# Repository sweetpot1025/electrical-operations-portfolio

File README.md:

# 郭浩田 · 电气工程项目作品集

**Haotian Guo | Electrical Engineering Portfolio**

河南理工大学电气工程及其自动化本科，悉尼大学电气工程硕士在读。关注电气运维、数据中心基础设施供配电、设备运行与故障分析。

项目覆盖井下供配电设计、三相电路与故障分析、电力系统动态稳定性、低压配电网全年仿真、光伏及风电实验，以及实习中的 PCB 设计和工程交付。通过手算、建模、测量和数据分析，解释从正常运行到故障、扰动及控制后的设备与系统表现。

## 项目目录

每个项目的页面包含任务、具体工作、模型或实验过程、关键结果，以及报告、数据或工程文件下载。

| 序号 | 项目 | 已完成的工作与可查看成果 |
|---|---|---|
| 01 | **[井下供配电一次系统设计](01-power-distribution-design.md)** | 本科毕设：负荷与无功分析、变压器和电缆选型、17 个短路点计算、设备校验、论文和电气主接线图 CAD |
| 02 | **[三相稳态建模、潮流与短路分析](02-short-circuit-analysis.md)** | ELEC5204：电阻/RL/非理想电源、七节点网络、三种变压器接线、三相及接地故障；两份报告和模型脚本 |
| 03 | **[单机与多机系统动态稳定性](03-dynamic-stability.md)** | ELEC5211：SMIB 功角、三机九节点潮流与无功补偿、动态初始化、故障清除、阻尼、CCT；两份报告及 23 幅成果图 |
| 04 | **[配电网、家庭储能与动态运行区间](04-distribution-network-and-storage.md)** | ELEC5208：36 用户三相四线模型、105,120 步全年分析、规则式/优化式 HEMS、SOCP DOE；三个阶段报告与工程代码 |
| 05 | **[电气测量、光伏控制与风电实验](05-energy-laboratory.md)** | ELEC5206：仪器、光伏特性、单二极管模型、PICAXE MPPT、风机测试、PMSG 联调；五份报告和测量数据 |
| 06 | **[温湿度传感器节点与 PCB 设计](06-internship-engineering.md)** | 施耐德实习：KiCad 原理图/PCB、制造与装配资料、ERC/DRC、版本复核、12 项样机验证计划 |
| 07 | **[考虑用户偏好与配网约束的 P2P 能源交易](07-capstone-research.md)** | 硕士研究进行中：研究提案、初始项目评估、交易机制及配电网约束分析 |

## 工程方法与工具

| 工作类型 | 方法与工具 |
|---|---|
| 供配电与故障 | 负荷计算、标幺制、戴维南等值、Zbus、对称分量、设备参数校验 |
| 稳态与动态建模 | MATLAB / Simulink、MATPOWER、ode45、功率平衡和相对功角分析 |
| 配电网与储能 | Julia / OpenDSS、全年时序潮流、SOC、分时电价、JuMP / HiGHS / Clarabel |
| 实验与数据 | 示波器、函数发生器、DACI / LVDAC-EMS、I-V / P-V 曲线、PWM、测量交叉核查 |
| 工程交付 | CAD、KiCad、Gerber / BOM / 装配资料、ERC / DRC、版本与测试记录 |

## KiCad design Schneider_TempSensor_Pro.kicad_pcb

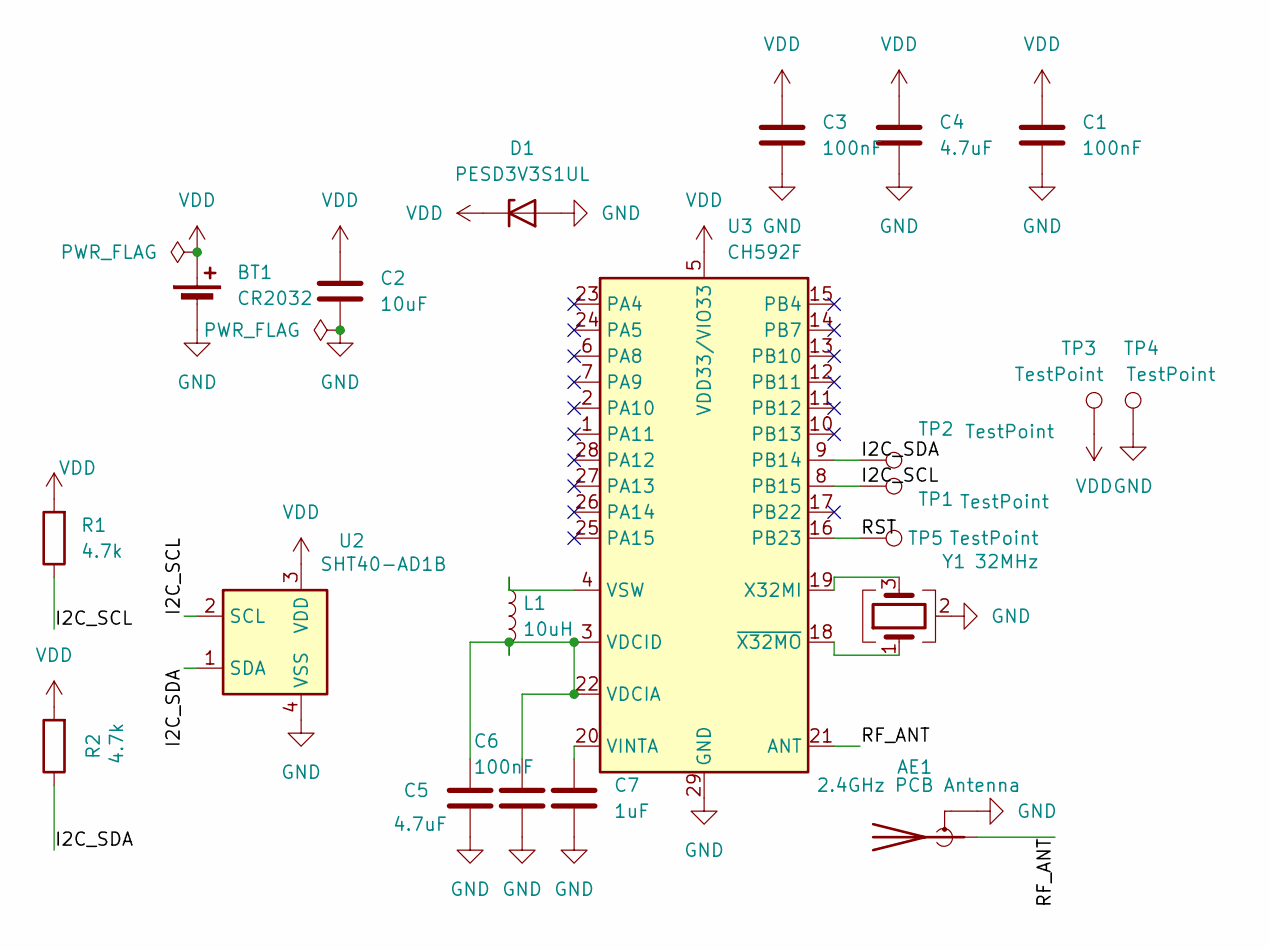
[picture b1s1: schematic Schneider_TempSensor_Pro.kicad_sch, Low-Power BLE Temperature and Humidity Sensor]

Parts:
AE1: 2.4GHz PCB Antenna; Texas_SWRA117D_2.4GHz_Left
BT1: CR2032; BatteryHolder_Keystone_1060_1x2032
C1: 100nF; C_0402_1005Metric
C2: 10uF; C_0603_1608Metric
C3, C6: 100nF; C_0603_1608Metric_Pad1.08x0.95mm_HandSolder
C4, C5: 4.7uF; C_0603_1608Metric_Pad1.08x0.95mm_HandSolder
C7: 1uF; C_0603_1608Metric_Pad1.08x0.95mm_HandSolder
D1: PESD3V3S1UL; D_SOD-882
L1: 10uH; L_0603_1608Metric_Pad1.05x0.95mm_HandSolder
R1, R2: 4.7k; R_0402_1005Metric
TP1, TP2, TP3, TP4, TP5: TestPoint; TestPoint_Pad_D1.0mm
U2: SHT40-AD1B; Sensirion_DFN-4_1.5x1.5mm_P0.8mm_SHT4x_NoCentralPad
U3: CH592F; WQFN-28-1EP_4x4mm_P0.4mm_EP2.7x2.7mm
Y1: 32MHz; Crystal_SMD_3225-4Pin_3.2x2.5mm

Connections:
/I2C_SCL: R1.1, TP1.1 (1_1), U2.2 (SCL), U3.8 (PB15)
/I2C_SDA: R2.1, TP2.1 (1_1), U2.1 (SDA), U3.9 (PB14)
/RF_ANT: AE1.1 (A), U3.21 (ANT)
/RST: TP5.1 (1_1), U3.16 (PB23)
GND: AE1.2 (Shield), BT1.2 (-), C1.2, C2.2, C3.2, C4.2, C5.2, C6.2, C7.2, D1.2 (A), TP4.1 (1_1), U2.4 (VSS), U3.29 (GND), Y1.2 (G), Y1.4 (G)
unnamed: C5.1, C6.1, L1.2, U3.3 (VDCID), U3.22 (VDCIA)
unnamed: C7.1, U3.20 (VINTA)
unnamed: L1.1, U3.4 (VSW)
unnamed: U3.19 (X32MI), Y1.3
unnamed: U3.18 (~X32MO), Y1.1
VDD: BT1.1 (+), C1.1, C2.1, C3.1, C4.1, D1.1 (K), R1.2, R2.2, TP3.1 (1_1), U2.3 (VDD), U3.5 (VDD33/VIO33)

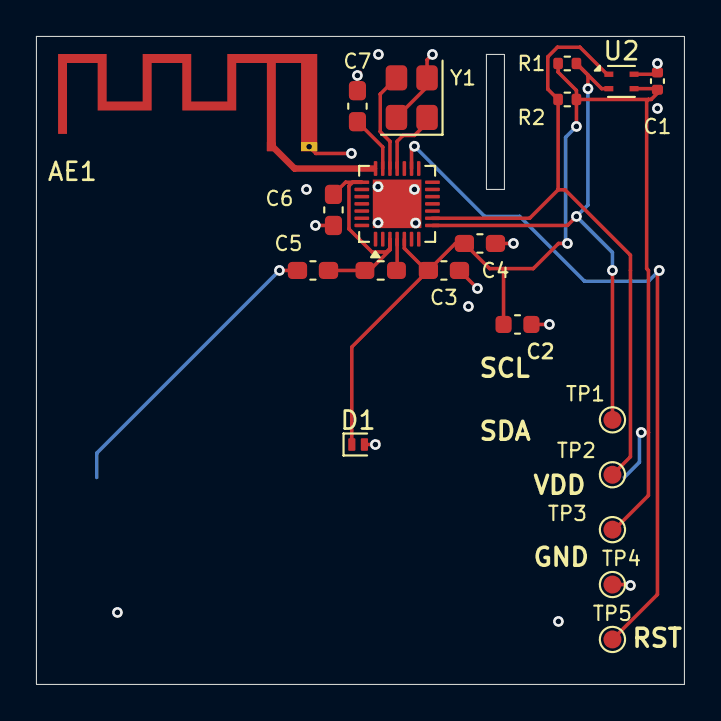
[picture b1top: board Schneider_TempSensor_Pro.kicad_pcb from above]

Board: 4 copper layers, 36.0 x 36.0 mm, 21 parts (1 on the bottom side), 11 nets.
